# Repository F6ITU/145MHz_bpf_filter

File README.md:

# 145MHz_bpf_filter
140-150 MHz bpf filter using MCL module for EU2AV transverter

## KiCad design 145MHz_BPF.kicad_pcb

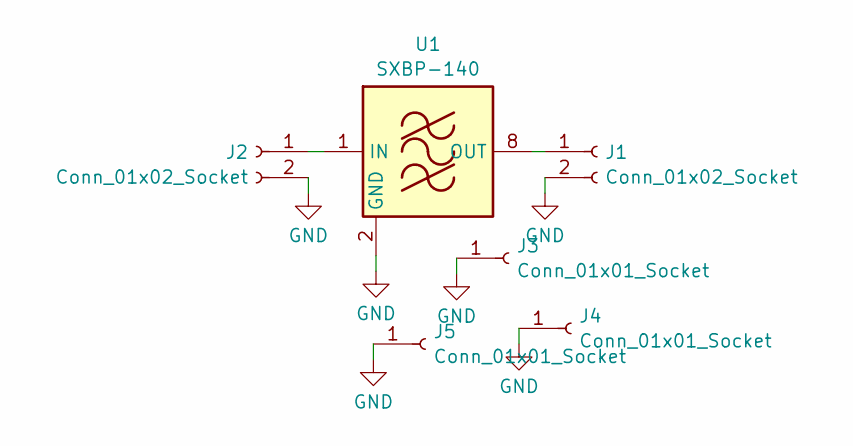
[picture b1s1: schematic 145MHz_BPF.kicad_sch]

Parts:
J1, J2: Conn_01x02_Socket; MMCX_Molex_73415-1471_Vertical
J3, J4, J5: Conn_01x01_Socket; SolderWire-0.1sqmm_1x01_D0.4mm_OD1mm
U1: SXBP-140; Mini-Circuits_HF1139_LandPatternPL-230

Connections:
GND: J1.2, J2.2, J3.1, J4.1, J5.1, U1.2 (GND), U1.3 (GND), U1.4 (GND), U1.5 (GND), U1.6 (GND), U1.7 (GND)
unnamed: J1.1, U1.8 (OUT)
unnamed: J2.1, U1.1 (IN)

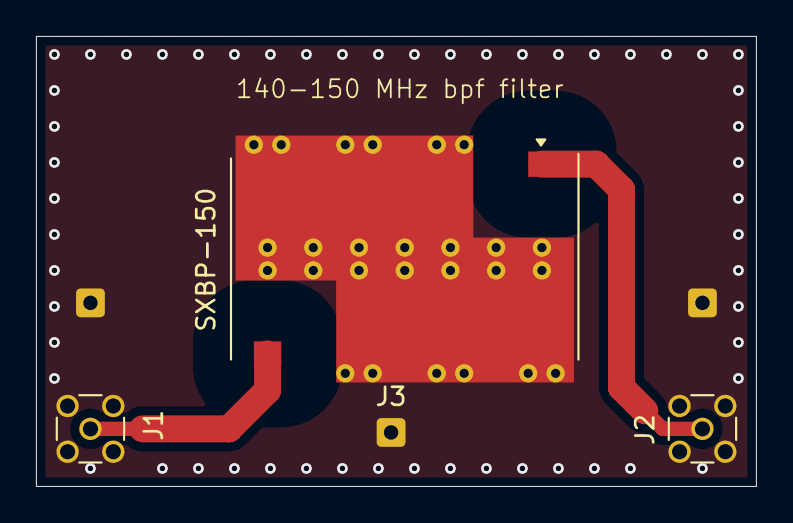
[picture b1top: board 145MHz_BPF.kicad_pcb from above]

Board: 2 copper layers, 40.0 x 25.0 mm, 6 parts (0 on the bottom side), 3 nets.

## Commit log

2024-06-27 initial release, do not use it yet
2024-06-28 3D module added, error in gnd strap fixed
2024-07-10 final release, Gerber ok
2024-07-11 mmcx connector footprint added
2024-07-11 new gerber
